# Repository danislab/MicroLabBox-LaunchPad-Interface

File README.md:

# dSPACE MicroLabBox TI LaunchPad Interface PCB

The MicroLabBox LaunchPad Interface is a simple PCB to connect LaunchPads from Texas Instruments (TI) to the MicroLabBox from dSPACE to perform real-time Hardware-in-the-Loop (HIL) tests. This Interface PCB can be used to accelerate the development and validation of software and algorithms running on MCUs from TI.
Depending on the LaunchPad the interface PCB offers up to 28 digital IOs, 16 analog inputs (LaunchPad side), 4 analog outputs (LaunchPad side) and two independent CAN interfaces.

## Status
* The Interface PCB was tested with LaunchPads for the TI MCUs F28377S, 570LS12x and 570LC43x.
* The position of the CAN connector for the dSPACE MicroLabBox is not correct aligned with the connectors of the connector group B. As workaround, a straight D-sub connector can be connected with wires to the PCB. In a future release this problem will be solved with a connector that is in line with the other two 50 pol connectors of the connector group B.

## Connectors
* J1 - J4 are used to connect the LaunchPad to the Interface PCB. The labelling and pin assignment follows the TIBoosterPack standard from Texas Instruments.
* J5 is used to connect the Interface PCB to the digital IOs from the dSPACE MicroLabBox. The connector is made of machined contacts which minimises wear and tear of the MicroLabBox connectors.
* J6 is used to connect the Interface PCB to the analogue IOs from the dSPACE MicroLabBox. The connector is made of machined contacts which minimises wear and tear of the MicroLabBox connectors.
* J7 is used to connect the Interface PCB to the two CAN interface of the dSPACE MicroLabBox. The connector is made of machined contacts which minimises wear and tear of the MicroLabBox connectors.
* J8 - J9 are used to connect a external CAN interface over a 9 pin D-sub. E.g. Vector, PEAK, Kvaser...
* J10 and J13 are used for the CAN Rx and Tx pins of the MCU.
* J11 and J14 are used for CAN high and CAN low for the CAN transceiver in case one is already soldered to the LanchPad.
* J12 and J15 are used to enable the 120Ohm terminator resistor for the CAN interface.

## Pinout
The pinout of the CAN interface follows the ISO 11898 specification
* Pin 2 is for CAN low
* Pin 7 is for CAN high

The pinout of the connectors J1 - J4 is described in the following table.

| TIBoosterPack standard    |     | F28377S  | F28379D  | TMS 570LS12x and TMS 570LC43x  | dSPace MicroLabBox |     |          |
|---------------------------|-----|----------|----------|--------------------------------|--------------------|-----|----------|
| Connector                 | Pin | Function | Function | Function                       | Connector          | Pin | Function |
| J1                        | 1   | +3.3 V   | +3.3V    | +3.3 V                         |                    |     |          |
| J1                        | 2   | GPIO71   | GPIO32   | AD1IN[16]                      |                    |     |          |
| J1                        | 3   | GPIO90   | GPIO19   | SCIRX                          |                    |     |          |
| J1                        | 4   | GPIO89   | GPIO18   | SCITX                          |                    |     |          |
| J1                        | 5   | GPIO41   | GPIO67   | GIOA[7]                        | Digital I/O B      | 33  | DIO2ch1  |
| J1                        | 6   | NC       | GPIO111  | AD1IN[17]                      |                    |     |          |
| J1                        | 7   | GPIO60   | GPIO60   | MIBSPI3CLK                     |                    |     |          |
| J1                        | 8   | GPIO61   | GPIO22   | GIOA[6]                        | Digital I/O B      | 32  | DIO2ch2  |
| J1                        | 9   | GPIO43   | GPIO105  | N2HET1[4]                      | Digital I/O B      | 31  | DIO2ch3  |
| J1                        | 10  | GPIO42   | GPIO104  | N2HET1[9]                      | Digital I/O B      | 29  | DIO2ch4  |
|                           |     |          |          |                                |                    |     |          |
| J2                        | 20  | GND      | GND      | GND                            |                    |     |          |
| J2                        | 19  | GPIO4    | GPIO61   | N2HET1[22]                     |                    |     |          |
| J2                        | 18  | GPIO62   | GPIO123  | MIBSPI3NCS[1]                  |                    |     |          |
| J2                        | 17  | NC       | GPIO122  | GIOB[3]                        |                    |     |          |
| J2                        | 16  | RESET    | RESET    | RESET                          |                    |     |          |
| J2                        | 15  | GPIO58   | GPIO58   | MIBSPI3SIMO                    |                    |     |          |
| J2                        | 14  | GPIO59   | GPIO59   | MIBSPI3SOMI                    |                    |     |          |
| J2                        | 13  | GPIO72   | GPIO124  | N2HET1[27]                     | Digital I/O B      | 28  | DIO2ch5  |
| J2                        | 12  | GPIO73   | GPIO125  | N2HET1[29]                     | Digital I/O B      | 27  | DIO2ch6  |
| J2                        | 11  | GPIO78   | GPIO29   | GIOB[2]                        | Digital I/O B      | 25  | DIO2ch7  |
|                           |     |          |          |                                |                    |     |          |
| J3                        | 21  | +5 V     | +5 V     | +5 V                           |                    |     |          |
| J3                        | 22  | GND      | GND      | GND                            |                    |     |          |
| J3                        | 23  | ADCIN14  | ADCIN14  | AD1[0]                         | Analog I/O B       | 49  | AO1ch1   |
| J3                        | 24  | ADCINB1  | ADCINC3  | AD1[7]                         | Analog I/O B       | 32  | AO1ch2   |
| J3                        | 25  | ADCINB4  | ADCINB3  | AD1IN[18]                      | Analog I/O B       | 47  | AO1ch3   |
| J3                        | 26  | ADCINB2  | ADCINA3  | AD1IN[19]                      | Analog I/O B       | 30  | AO1ch4   |
| J3                        | 27  | ADCINA0  | ADCINC2  | AD1IN[20]                      | Analog I/O B       | 45  | AO1ch5   |
| J3                        | 28  | ADCINB0  | ADCINB2  | AD1IN[21]                      | Analog I/O B       | 28  | AO1ch6   |
| J3                        | 29  | ADCINA1  | ADCINA2  |                                | Analog I/O B       | 43  | AO1ch7   |
| J3                        | 30  | NC       | ADCINA0  |                                | Analog I/O B       | 26  | AO1ch8   |
|                           |     |          |          |                                |                    |     |          |
| J4                        | 40  | GPIO12   | GPIO0    | N2HET1[20]                     | Digital I/O B      | 17  | DIO1ch33 |
| J4                        | 39  | GPIO13   | GPIO1    | N2HET1[18]                     | Digital I/O B      | 16  | DIO1ch34 |
| J4                        | 38  | GPIO14   | GPIO2    | N2HET1[16]                     | Digital I/O B      | 15  | DIO1ch35 |
| J4                        | 37  | GPIO15   | GPIO3    | N2HET1[30]                     | Digital I/O B      | 14  | DIO1ch36 |
| J4                        | 36  | GPIO16   | GPIO4    | N2HET1[14]                     | Digital I/O B      | 13  | DIO1ch37 |
| J4                        | 35  | GPIO17   | GPIO5    | N2HET1[12]                     | Digital I/O B      | 12  | DIO1ch38 |
| J4                        | 34  | GPIO20   | GPIO24   | GIOA[5]                        | Digital I/O B      | 11  | DIO1ch39 |
| J4                        | 33  | GPIO21   | GPIO16   | GIOA[2]                        | Digital I/O B      | 10  | DIO1ch40 |
| J4                        | 32  | DAC1     | DAC1     | GIOA[1]                        | Analog I/O B       | 17  | AI2ch1   |
| J4                        | 31  | DAC2     | DAC2     | GIOA[0]                        | Analog I/O B       | 15  | AI2ch2   |
|                           |     |          |          |                                |                    |     |          |
| J6                        | 41  | +3.3 V   | +3.3 V   | +3.3 V                         |                    |     |          |
| J6                        | 42  | NC       | GPIO95   | AD1IN[9]                       |                    |     |          |
| J6                        | 43  | GPIO87   | GPIO139  | LIN1_RXD                       |                    |     |          |
| J6                        | 44  | GPIO86   | GPIO56   | LIN1_TXD                       |                    |     |          |
| J6                        | 45  | NC       | GPIO97   | GIOB[2]                        |                    |     |          |
| J6                        | 46  | NC       | GPIO94   | AD1IN[1]                       |                    |     |          |
| J6                        | 47  | GPIO65   | GPIO65   | MIBSPI1CLK                     | Digital I/O B      | 24  | DIO2ch8  |
| J6                        | 48  | NC       | GPIO52   | N2HET1[31]                     | Digital I/O B      | 23  | DIO2ch9  |
| J6                        | 49  | GPIO69   | GPIO41   | N2HET1[24]                     |                    |     |          |
| J6                        | 50  | GPIO66   | GPIO40   | N2HET1[26]                     |                    |     |          |
|                           |     |          |          |                                |                    |     |          |
| J7                        | 60  | GND      | GND      | GND                            |                    |     |          |
| J7                        | 59  | GPIO91   | GPIO66   | N2HET2[8]                      |                    |     |          |
| J7                        | 58  | NC       | GPIO131  | MIBSPI1SOMI[1]                 |                    |     |          |
| J7                        | 57  | NC       | GPIO130  | MIBSPI5SIMO[0]                 |                    |     |          |
| J7                        | 56  | RESET    | RESET    | RESET                          |                    |     |          |
| J7                        | 55  | GPIO63   | GPIO63   | MIBSPI1SIMO                    |                    |     |          |
| J7                        | 54  | GPIO64   | GPIO64   | MIBSPI1SOMI                    |                    |     |          |
| J7                        | 53  | GPIO99   | GPIO26   | N2HET1[17]                     | Digital I/O B      | 21  | DIO2ch10 |
| J7                        | 52  | GPIO92   | GPIO27   | N2HET1[19]                     | Digital I/O B      | 20  | DIO2ch11 |
| J7                        | 51  | NC       | GPIO25   | MIBSPI5SOMI[0]                 | Digital I/O B      | 19  | DIO2ch12 |
|                           |     |          |          |                                |                    |     |          |
| J8                        | 61  | +5 V     | +5 V     | +5 V                           |                    |     |          |
| J8                        | 62  | GND      | GND      | GND                            |                    |     |          |
| J8                        | 63  | ADCIN15  | ADCIN15  | AD1IN[10]                      | Analog I/O B       | 41  | AO1ch9   |
| J8                        | 64  | ADCINA2  | ADCINC5  | AD1IN[2]                       | Analog I/O B       | 24  | AO1ch10  |
| J8                        | 65  | ADCINA5  | ADCINB5  | AD1IN[3]                       | Analog I/O B       | 39  | AO1ch11  |
| J8                        | 66  | ADCINB5  | ADCINA5  | AD1IN[11]                      | Analog I/O B       | 22  | AO1ch12  |
| J8                        | 67  | ADCINA3  | ADCINC4  | AD1IN[4]                       | Analog I/O B       | 37  | AO1ch13  |
| J8                        | 68  | ADCINB3  | ADCINB4  | AD1IN[12]                      | Analog I/O B       | 20  | AO1ch14  |
| J8                        | 69  | ADCINA4  | ADCINA4  | NC                             | Analog I/O B       | 35  | AO1ch15  |
| J8                        | 70  | NC       | ADCINA1  | NC                             | Analog I/O B       | 18  | AO1ch16  |
|                           |     |          |          |                                |                    |     |          |
| J9                        | 80  | GPIO2    | GPIO6    | N2HET1[10]                     | Digital I/O B      | 9   | DIO1ch41 |
| J9                        | 79  | GPIO3    | GPIO7    | N2HET1[28]                     | Digital I/O B      | 8   | DIO1ch42 |
| J9                        | 78  | GPIO10   | GPIO8    | N2HET1[8]                      | Digital I/O B      | 7   | DIO1ch43 |
| J9                        | 77  | GPIO11   | GPIO9    | N2HET1[23]                     | Digital I/O B      | 6   | DIO1ch44 |
| J9                        | 76  | GPIO18   | GPIO10   | MIBSPI5NENA                    | Digital I/O B      | 5   | DIO1ch45 |
| J9                        | 75  | GPIO19   | GPIO11   | N2HET2[18]                     | Digital I/O B      | 4   | DIO1ch46 |
| J9                        | 74  | NC       | GPIO14   | GIOB[1]                        | Digital I/O B      | 3   | DIO1ch47 |
| J9                        | 73  | NC       | GPIO15   | GIOB[0]                        | Digital I/O B      | 2   | DIO1ch48 |
| J9                        | 72  | DAC3     | DAC3     | AD1EVT                         | Analog I/O B       | 13  | AI2ch3   |
| J9                        | 71  | DAC4     | DAC4     | MIBSPI5CLK                     | Analog I/O B       | 11  | AI2ch4   |

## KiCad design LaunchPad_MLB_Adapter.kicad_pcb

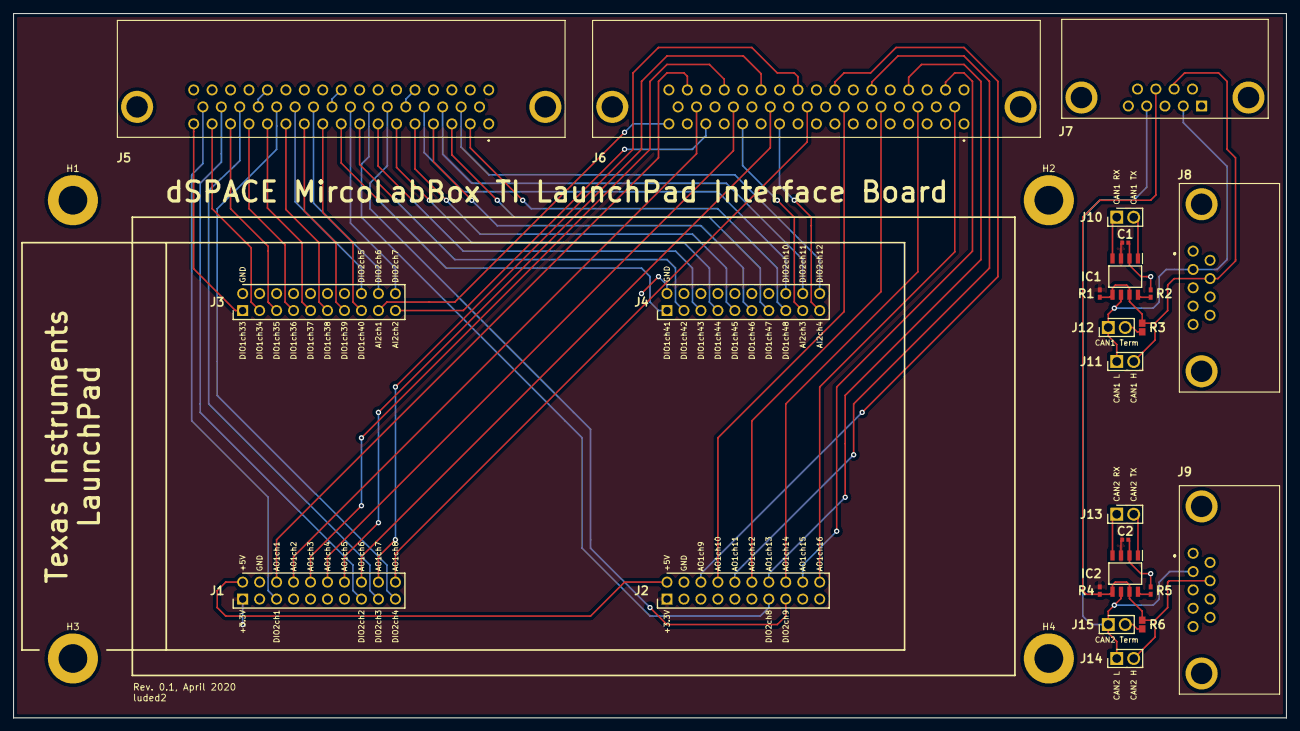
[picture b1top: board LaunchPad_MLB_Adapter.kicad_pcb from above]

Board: 2 copper layers, 190.5 x 105.4 mm, 29 parts (0 on the bottom side), 63 nets.

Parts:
C1, C2: GRM155R61A104KA01D; CAPC1005X55N
H1, H2, H3, H4: MountingHole_Pad; MountingHole_4.3mm_M4_DIN965_Pad
IC1, IC2: SN65HVD234DR; SOIC127P600X175-8N
J1, J2, J3, J4: 61302021121; HDRV20W64P254X254_2X10_2540X508X869P
J5, J6: 09665627812
J7: 09661626812
J8, J9: 09661526613
J10, J11, J12, J13, J14, J15: 61300211121; HDRV2W110P0X254_1X2_508X254X854P
R1, R2, R4, R5: RC0402FR-0710KL; RESC1005X40N
R3, R6: RC0603FR-07120RL; RESC1608X55N

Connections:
+3V3: C1.1, C2.1, IC1.3, IC2.3, J1.1, J2.1, R1.1, R4.1
+5V: J1.2, J2.2
/AI2ch1: J3.17, J6.17
/AI2ch2: J3.19, J6.15
/AI2ch3: J4.17, J6.13
/AI2ch4: J4.19, J6.11
/AO1ch1: J1.6, J6.49
/AO1ch2: J1.8, J6.32
/AO1ch3: J1.10, J6.47
/AO1ch4: J1.12, J6.30
/AO1ch5: J1.14, J6.45
/AO1ch6: J1.16, J6.28
/AO1ch7: J1.18, J6.43
/AO1ch8: J1.20, J6.26
/AO1ch9: J2.6, J6.41
/AO1ch10: J2.8, J6.24
/AO1ch11: J2.10, J6.39
/AO1ch12: J2.12, J6.22
/AO1ch13: J2.14, J6.37
/AO1ch14: J2.16, J6.20
/AO1ch15: J2.18, J6.35
/AO1ch16: J2.20, J6.18
/CANHch1: IC1.5, IC1.7, J7.7, J8.7, J11.2, R1.2, R3.2
/CANHch2: IC2.5, IC2.7, J7.8, J9.7, J14.2, R4.2, R6.2
/CANLch1: IC1.6, J7.2, J8.2, J11.1, J12.1
/CANLch2: IC2.6, J7.4, J9.2, J14.1, J15.1
/DIO1ch33: J3.1, J5.17
/DIO1ch34: J3.3, J5.16
/DIO1ch35: J3.5, J5.15
/DIO1ch36: J3.7, J5.14
/DIO1ch37: J3.9, J5.13
/DIO1ch38: J3.11, J5.12
/DIO1ch39: J3.13, J5.11
/DIO1ch40: J3.15, J5.10
/DIO1ch41: J4.1, J5.9
/DIO1ch42: J4.3, J5.8
/DIO1ch43: J4.5, J5.7
/DIO1ch44: J4.7, J5.6
/DIO1ch45: J4.9, J5.5
/DIO1ch46: J4.11, J5.4
/DIO1ch47: J4.13, J5.3
/DIO1ch48: J4.15, J5.2
/DIO2ch1: J1.5, J5.33
/DIO2ch2: J1.15, J5.32
/DIO2ch3: J1.17, J5.31
/DIO2ch4: J1.19, J5.29
/DIO2ch5: J3.16, J5.28
/DIO2ch6: J3.18, J5.27
/DIO2ch7: J3.20, J5.25
/DIO2ch8: J2.13, J5.24
/DIO2ch9: J2.15, J5.23
/DIO2ch10: J4.16, J5.21
/DIO2ch11: J4.18, J5.20
/DIO2ch12: J4.20, J5.19
GND: C1.2, C2.2, IC1.2, IC2.2, J1.4, J2.4, J3.2, J4.2, J5.1, J5.18, J5.22, J5.26, J5.30, J5.34, J5.38, J5.42, J5.46, J5.50, J5.MH1, J5.MH2, J6.1, J6.2, J6.4, J6.6, J6.8, J6.10, J6.12, J6.14, J6.16, J6.34, J6.36, J6.38, J6.40, J6.42, J6.44, J6.46, J6.48, J6.50, J6.MH1, J6.MH2, J7.3, J7.MH1, J7.MH2, J8.MH1, J8.MH2, J9.MH1, J9.MH2, R2.2, R5.2
unnamed: IC1.1, J10.2
unnamed: IC1.4, J10.1
unnamed: IC1.8, R2.1
unnamed: IC2.1, J13.2
unnamed: IC2.4, J13.1
unnamed: IC2.8, R5.1
unnamed: J12.2, R3.1
unnamed: J15.2, R6.1

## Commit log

2020-10-23 added KiCad projetct files and customer library
2020-10-24 Added image of PCB for Readme
2020-10-24 Added brief description of interface to Readme
2020-10-24 new picture and extended gitignore
